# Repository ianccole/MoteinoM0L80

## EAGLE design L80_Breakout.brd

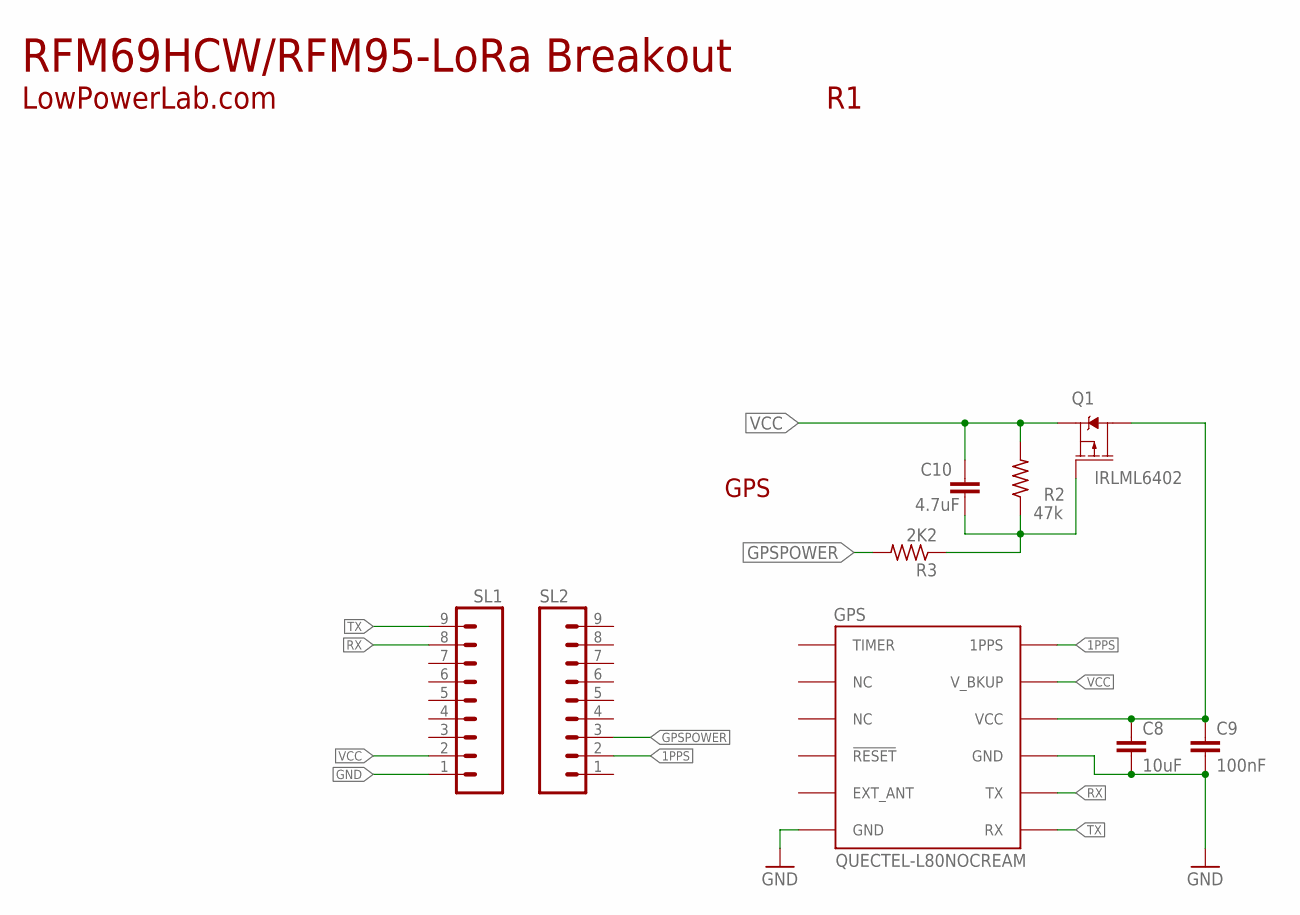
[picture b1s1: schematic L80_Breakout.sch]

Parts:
C8: 10uF; C0603-THINCREAM
C9: 100nF; C0603-THINCREAM; MPN 02016D104KAT2A
C10: 4.7uF; C0603-THINCREAM
GPS: QUECTEL-L80NOCREAM; QUECTEL-L80-NOCREAM
Q1: IRLML6402; SOT23-3
R2: 47k; R0603-THINCREAM
R3: 2K2; R0603-THINCREAM
SL1, SL2: M09; 09P

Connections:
1PPS: GPS.6 (1PPS), SL2.2
GND: C8.2, C9.2, GPS.3 (GND), GPS.12 (GND), SL1.1
GPSPOWER: R3.2, SL2.3
unnamed: C8.1, C9.1, GPS.4 (VCC), Q1.3 (D)
unnamed: C10.2, Q1.1 (G), R2.1, R3.1
RX: GPS.2 (TX), SL1.8
TX: GPS.1 (RX), SL1.9
VCC: C10.1, GPS.5 (V_BKUP), Q1.2 (S), R2.2, SL1.2

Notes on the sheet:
LowPowerLab.com
RFM69HCW/RFM95-LoRa Breakout
GPS

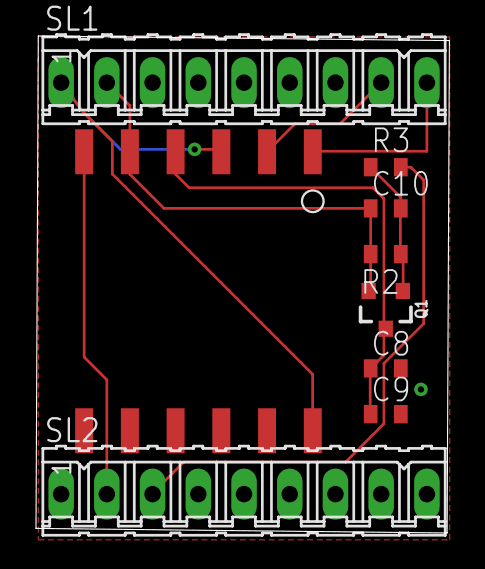
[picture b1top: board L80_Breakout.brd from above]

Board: 2 copper layers, 23.0 x 27.6 mm, 9 parts (0 on the bottom side), 8 nets.

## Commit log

2021-05-05 L80 M0 Breakout initial
2021-05-05 L80 M0 Breakout initial alt
